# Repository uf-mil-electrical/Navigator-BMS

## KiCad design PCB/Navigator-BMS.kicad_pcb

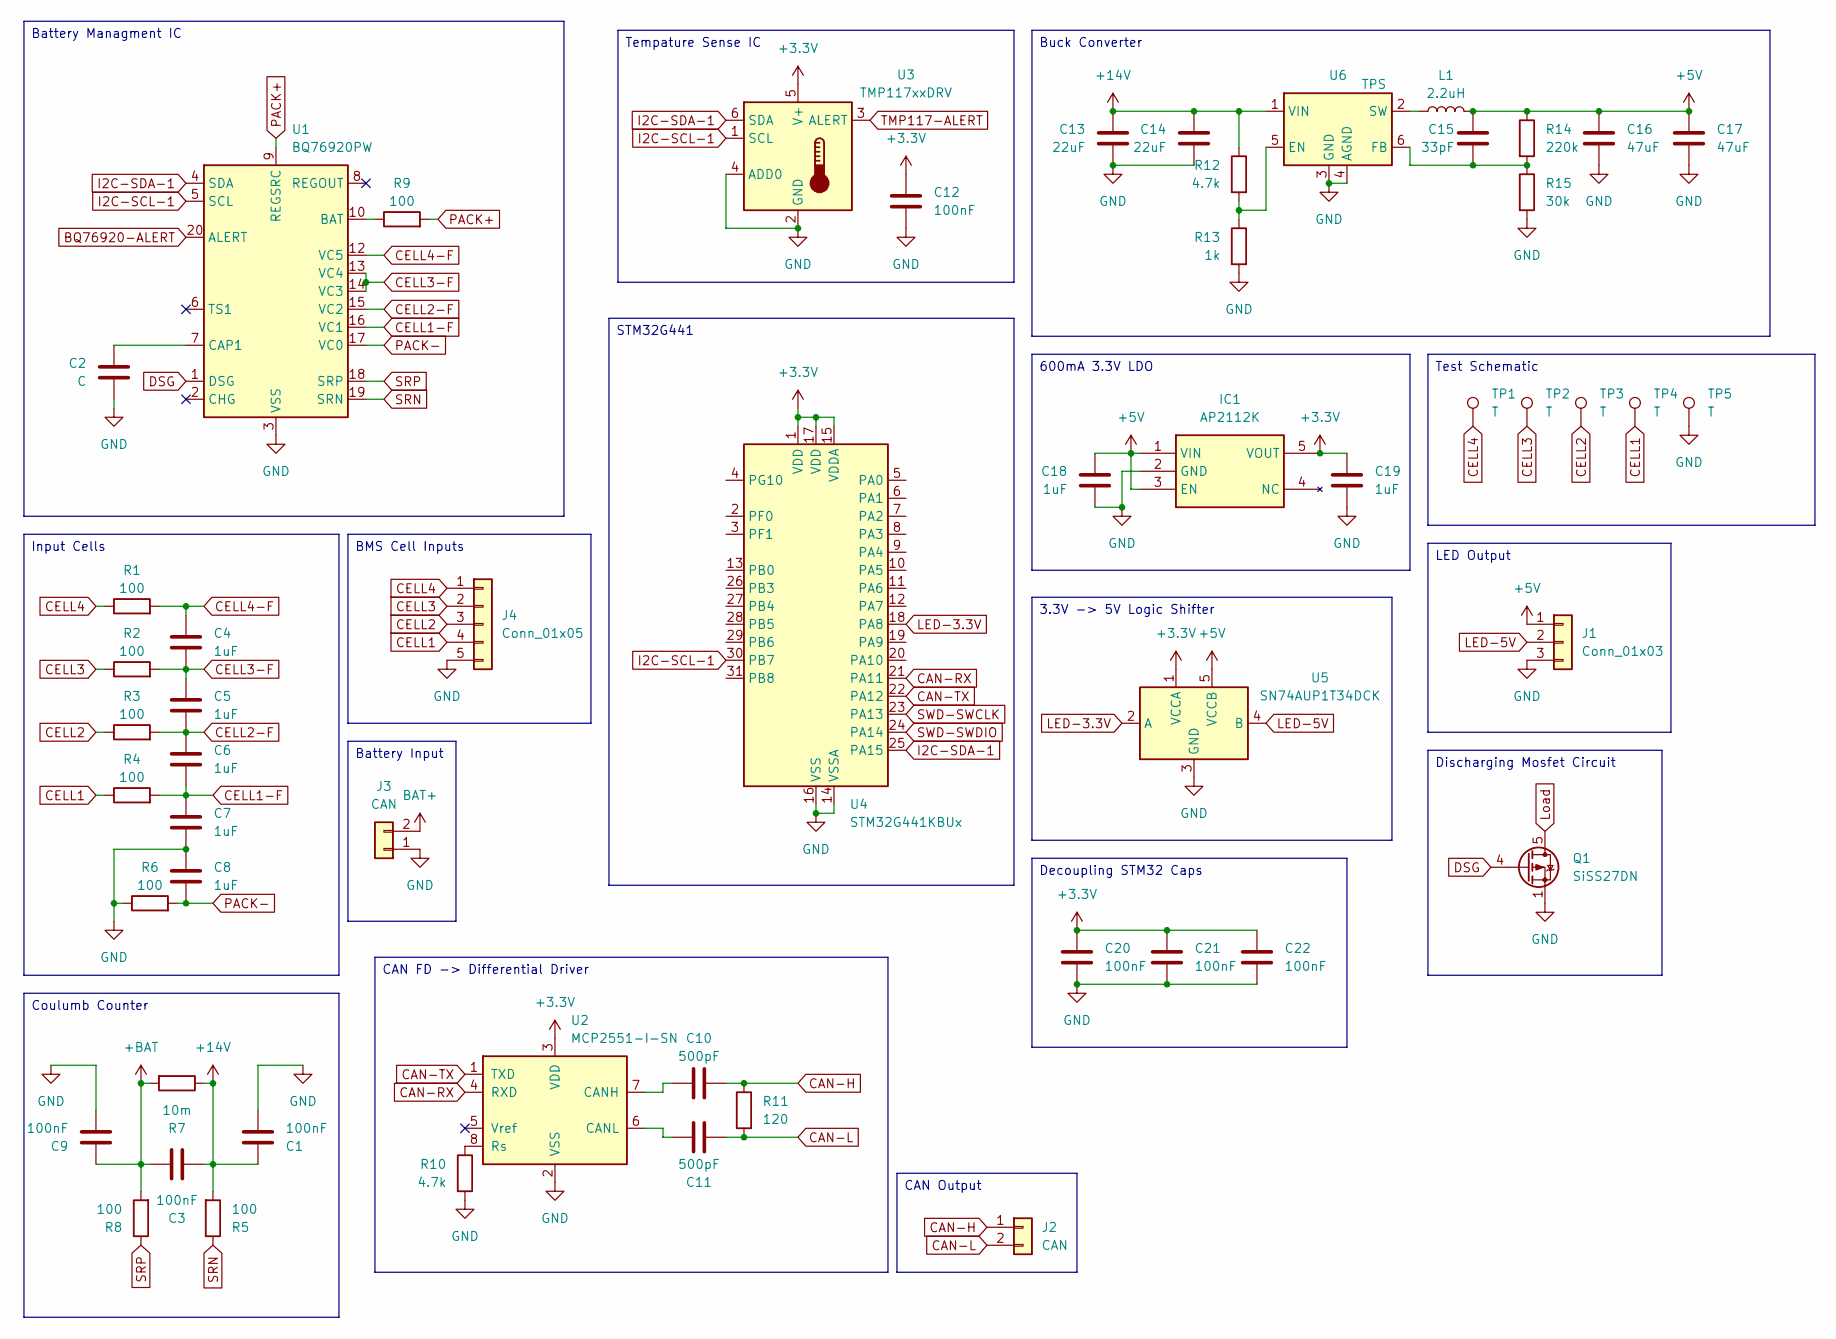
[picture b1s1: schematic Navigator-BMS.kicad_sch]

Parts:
C1, C3, C9, C12, C20, C21, C22: 100nF; C_0402_1005Metric
C2: C; C_0402_1005Metric
C4, C5, C6, C7, C8, C18, C19: 1uF; C_0402_1005Metric
C10, C11: 500pF; C_0402_1005Metric
C13, C14: 22uF; C_0805_2012Metric
C15: 33pF; C_0402_1005Metric
C16, C17: 47uF; C_0805_2012Metric
IC1: AP2112K; SOT95P285X140-5N; Mouser Part Number 621-AP2112K-3.3TRG1
J1: Conn_01x03; TerminalBlock_MaiXu_MX126-5.0-03P_1x03_P5.00mm
J2: CAN; TerminalBlock_Xinya_XY308-2.54-2P_1x02_P2.54mm_Horizontal
J3: CAN; AMASS_XT60-F_1x02_P7.20mm_Vertical
J4: Conn_01x05; JST_EH_B5B-EH-A_1x05_P2.50mm_Vertical
L1: 2.2uH; L_Coilcraft_XAL5030-XXX
Q1: SiSS27DN; Vishay_PowerPAK_1212-8_Single
R1, R2, R3, R4, R5, R6, R8, R9: 100; R_0402_1005Metric
R7: 10m; R_2512_6332Metric
R10, R12: 4.7k; R_0402_1005Metric
R11: 120; R_0402_1005Metric
R13: 1k; R_0402_1005Metric
R14: 220k; R_0402_1005Metric
R15: 30k; R_0402_1005Metric
TP1, TP2, TP3, TP4, TP5: T; TestPoint_Pad_1.0x1.0mm
U1: BQ76920PW; TSSOP-20_4.4x6.5mm_P0.65mm
U2: MCP2551-I-SN; SOIC-8_3.9x4.9mm_P1.27mm
U3: TMP117xxDRV; WSON-6-1EP_2x2mm_P0.65mm_EP1x1.6mm
U4: STM32G441KBUx; QFN-32-1EP_5x5mm_P0.5mm_EP3.45x3.45mm
U5: SN74AUP1T34DCK; SOT-353_SC-70-5
U6: TPS; SOTFL50P160X60-6N

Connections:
+3.3V: C12.1, C19.1, C20.1, C21.1, C22.1, IC1.5 (VOUT), U2.3 (VDD), U3.5 (V+), U4.1 (VDD), U4.15 (VDDA), U4.17 (VDD), U5.1 (VCCA)
+5V: C15.1, C16.1, C17.1, C18.1, IC1.1 (VIN), IC1.3 (EN), J1.1, L1.2, R14.1, U5.5 (VCCB)
+14V: C1.1, C3.1, C13.1, C14.1, R5.2, R7.1, R12.1, U6.1 (VIN)
+BAT: C3.2, C9.1, R7.2, R8.2
BAT+: J3.2
BQ76920-ALERT: U1.20 (ALERT)
CAN-H: C10.2, J2.1, R11.1
CAN-L: C11.1, J2.2, R11.2
CAN-RX: U2.4 (RXD), U4.21 (PA11)
CAN-TX: U2.1 (TXD), U4.22 (PA12)
CELL1: J4.4, R4.1, TP4.1; also elsewhere on the board
CELL1-F: C6.2, C7.1, R4.2, U1.16 (VC1)
CELL2: J4.3, R3.1, TP3.1; also elsewhere on the board
CELL2-F: C5.2, C6.1, R3.2, U1.15 (VC2)
CELL3: J4.2, R2.1, TP2.1; also elsewhere on the board
CELL3-F: C4.2, C5.1, R2.2, U1.13 (VC4), U1.14 (VC3)
CELL4: J4.1, R1.1, TP1.1; also elsewhere on the board
CELL4-F: C4.1, R1.2, U1.12 (VC5)
DSG: Q1.4 (G), U1.1 (DSG)
GND: C1.2, C2.2, C7.2, C8.1, C9.2, C12.2, C13.2, C14.2, C16.2, C17.2, C18.2, C19.2, C20.2, C21.2, C22.2, IC1.2 (GND), J1.3, J3.1, J4.5, Q1.1 (S), Q1.2 (S), Q1.3 (S), R6.1, R10.2, R13.2, R15.2, TP5.1, U1.3 (VSS), U2.2 (VSS), U3.2 (GND), U3.4 (ADD0), U4.14 (VSSA), U4.16 (VSS), U4.32 (VSS), U4.33 (VSS), U5.3 (GND), U6.3 (GND), U6.4 (AGND)
I2C-SCL-1: U1.5 (SCL), U3.1 (SCL), U4.30 (PB7)
I2C-SDA-1: U1.4 (SDA), U3.6 (SDA), U4.25 (PA15)
LED-3.3V: U4.18 (PA8), U5.2 (A)
LED-5V: J1.2, U5.4 (B)
unnamed: R9.1, U1.10 (BAT)
unnamed: C2.1, U1.7 (CAP1)
unnamed: C10.1, U2.7 (CANH)
unnamed: C11.2, U2.6 (CANL)
unnamed: R10.1, U2.8 (Rs)
unnamed: R12.2, R13.1, U6.5 (EN)
unnamed: C15.2, R14.2, R15.1, U6.6 (FB)
unnamed: L1.1, U6.2 (SW)
PACK+: R9.2, U1.9 (REGSRC)
PACK-: C8.2, R6.2, U1.17 (VC0)
SRN: R5.1, U1.19 (SRN)
SRP: R8.1, U1.18 (SRP)
SWD-SWCLK: U4.23 (PA13)
SWD-SWDIO: U4.24 (PA14)
TMP117-ALERT: U3.3 (ALERT)

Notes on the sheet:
600mA 3.3V LDO
LED Output
Input Cells
Battery Input
STM32G441
CAN FD -> Differential Driver
3.3V -> 5V Logic Shifter
Test Schematic
Battery Managment IC
Tempature Sense IC
Buck Converter
BMS Cell Inputs
Coulumb Counter
Decoupling STM32 Caps
CAN Output
Discharging Mosfet Circuit

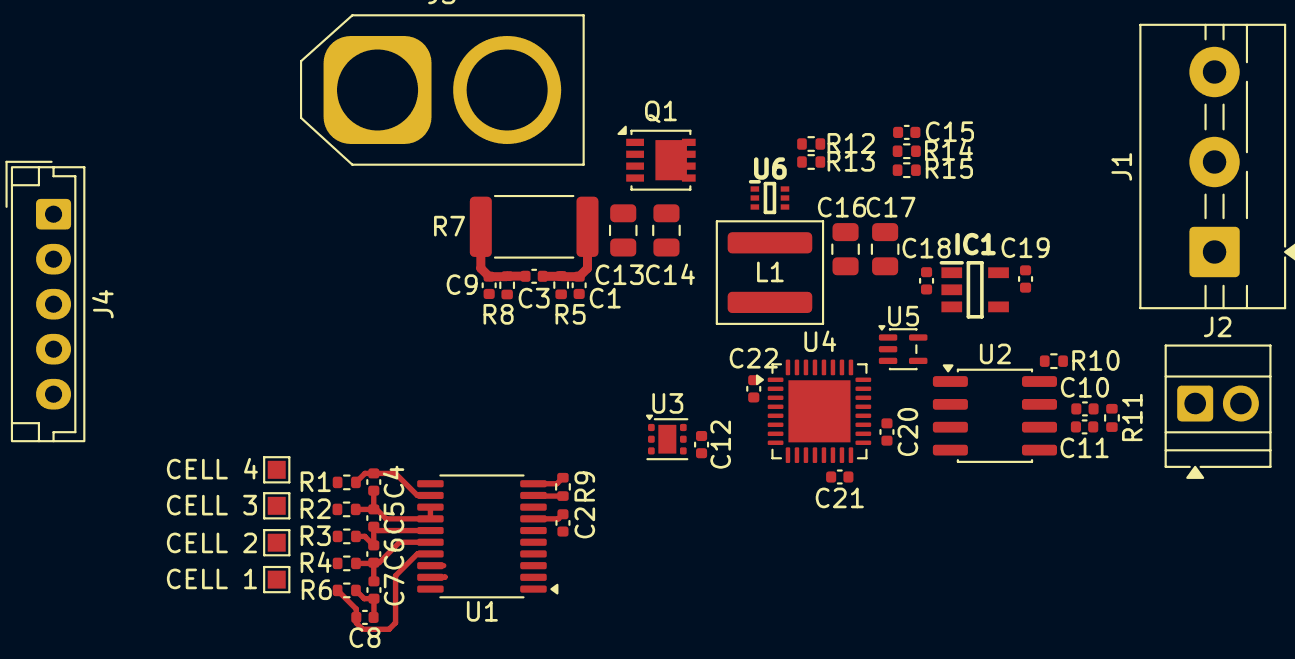
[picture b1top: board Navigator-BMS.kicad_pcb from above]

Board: 2 copper layers, 54 parts (0 on the bottom side), 34 nets.

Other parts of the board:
CELL 1, CELL 2, CELL 3, CELL 4: T; TestPoint_Pad_1.0x1.0mm

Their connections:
CELL1: CELL 1.1 (1_1); also elsewhere on the board
CELL2: CELL 2.1 (1_1); also elsewhere on the board
CELL3: CELL 3.1 (1_1); also elsewhere on the board
CELL4: CELL 4.1 (1_1); also elsewhere on the board

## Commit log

2026-04-27 Mostly Finished with the Schematic but I need more info on the connectors & I will probably switch the buck converter for a better current return path
2026-04-27 Almost done with the layout, still want info on the mosfets the labs use + the battery connectors
2026-04-30 Layout Considerations + Schematic almost done
2026-05-04 Finished layout. Board Shape kinda chopped but will be edited. Analog section far away from high current areas!
2026-05-14 Layout complete. Waiting to order + starting firmware using Russel's BQ76920 Test Board
2026-06-08 Firmware Update: Finished 2/3 of the main IC drivers (INA236 & TMP117). There is a bug on the BQ76920 Driver as it operates fine with the 3S battery that I have but it can't do the
